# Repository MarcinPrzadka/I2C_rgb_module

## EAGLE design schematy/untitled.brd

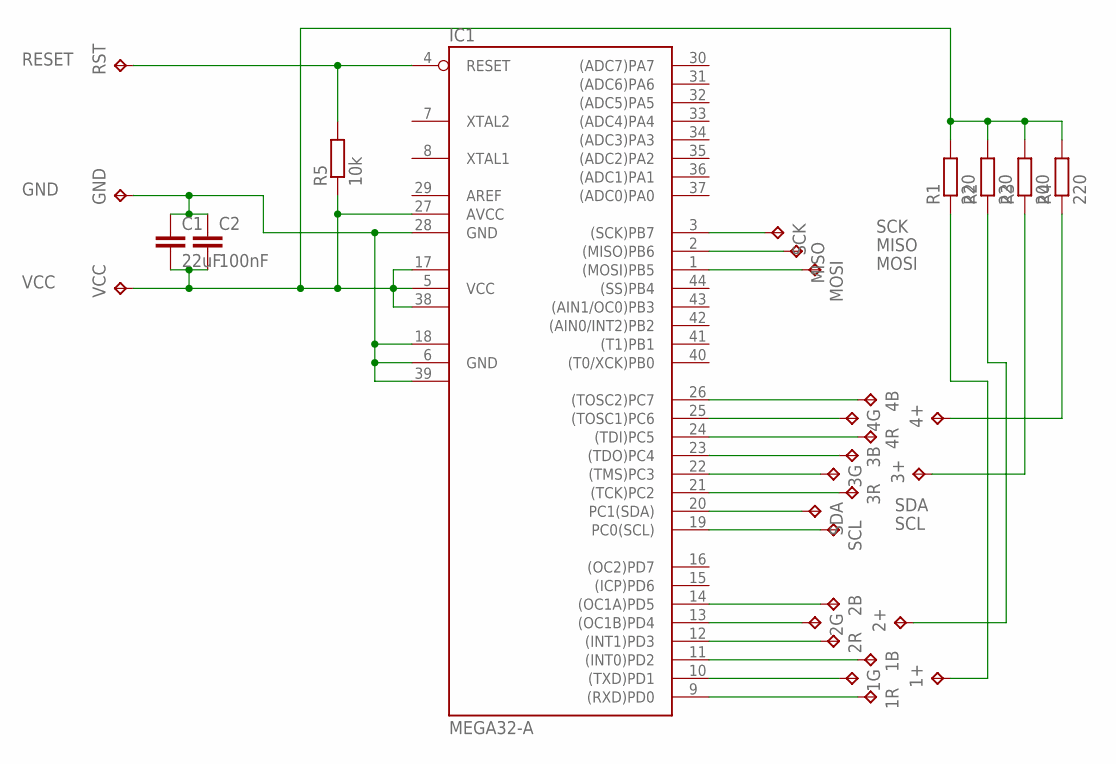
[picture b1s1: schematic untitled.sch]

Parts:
1+, 1B, 1G, 1R, 2+, 2B, 2G, 2R, 3+, 3B, 3G, 3R, 4+, 4B, 4G, 4R: TPTP19SQ; TP19SQ
C1: 22uF; C025-024X044
C2: 100nF; C025-024X044
GND: TPTP19SQ; TP19SQ
IC1: MEGA32-A; TQFP44
MISO: TPTP19SQ; TP19SQ
MOSI: TPTP19SQ; TP19SQ
R1, R2, R4: 220; M0805
R3: 200; M0805
R5: 10k; M0805
RST: TPTP19SQ; TP19SQ
SCK: SCK; TP19SQ
SCL: TPTP19SQ; TP19SQ
SDA: TPTP19SQ; TP19SQ
VCC: TPTP19SQ; TP19SQ

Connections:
GND: C1.1, C2.1, GND.TP, IC1.6 (GND), IC1.18 (GND1), IC1.28 (GND), IC1.39 (GND2)
MISO: IC1.2 ((MISO)PB6), MISO.TP
MOSI: IC1.1 ((MOSI)PB5), MOSI.TP
unnamed: 1R.TP, IC1.9 ((RXD)PD0)
unnamed: 1G.TP, IC1.10 ((TXD)PD1)
unnamed: 1B.TP, IC1.11 ((INT0)PD2)
unnamed: 2R.TP, IC1.12 ((INT1)PD3)
unnamed: 2G.TP, IC1.13 ((OC1B)PD4)
unnamed: 2B.TP, IC1.14 ((OC1A)PD5)
unnamed: 3R.TP, IC1.21 ((TCK)PC2)
unnamed: 3G.TP, IC1.22 ((TMS)PC3)
unnamed: 3B.TP, IC1.23 ((TDO)PC4)
unnamed: 4R.TP, IC1.24 ((TDI)PC5)
unnamed: 4G.TP, IC1.25 ((TOSC1)PC6)
unnamed: 4B.TP, IC1.26 ((TOSC2)PC7)
unnamed: 1+.TP, R1.1
unnamed: 2+.TP, R2.1
unnamed: 3+.TP, R3.1
unnamed: 4+.TP, R4.1
RESET: IC1.4 (RESET), R5.2, RST.TP
SCK: IC1.3 ((SCK)PB7), SCK.TP
SCL: IC1.19 (PC0(SCL)), SCL.TP
SDA: IC1.20 (PC1(SDA)), SDA.TP
VCC: C1.2, C2.2, IC1.5 (VCC), IC1.17 (VCC1), IC1.27 (AVCC), IC1.38 (VCC2), R1.2, R2.2, R3.2, R4.2, R5.1, VCC.TP

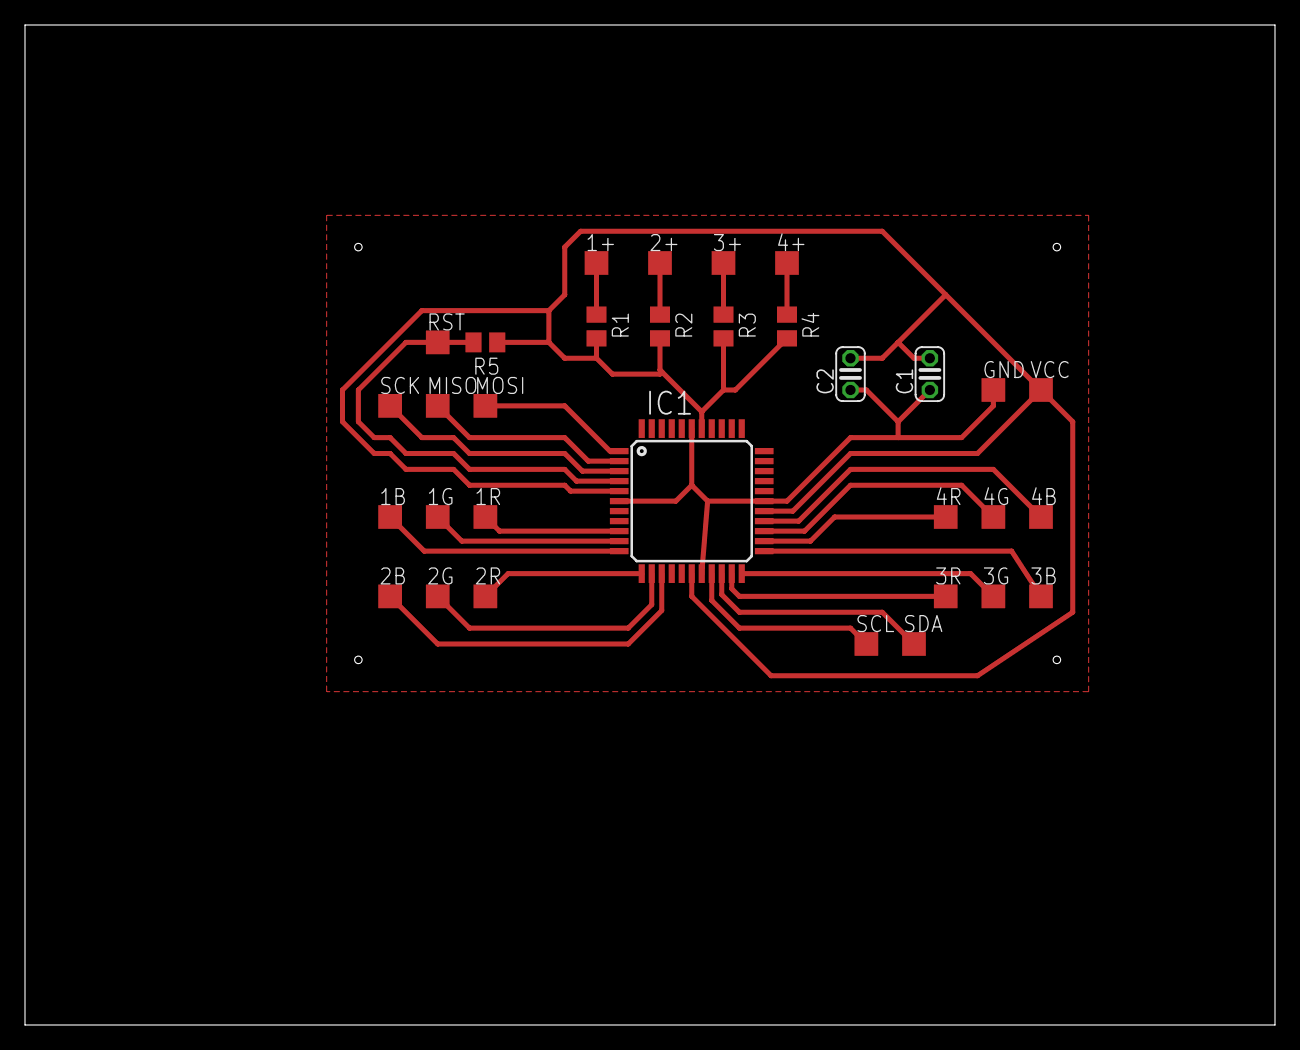
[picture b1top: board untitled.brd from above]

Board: 2 copper layers, 100.0 x 80.0 mm, 32 parts (0 on the bottom side), 24 nets.

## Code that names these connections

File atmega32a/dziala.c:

#include <avr/io.h>
#include <util/delay.h>
#include <avr/interrupt.h>

volatile uint8_t pwm1R, pwm1G, pwm1B, pwm2R, pwm2G, pwm2B,pwm3R, pwm3G, pwm3B, pwm4R, pwm4G, pwm4B;

int main(void)
{
	
	DDRB |= (1<<PB3);

	TCCR0 |= (1<<WGM01)|(1<<WGM00);		// tryb Fast PWM
	TCCR0 |= (1<<COM01);				// clear at TOP
	TCCR0 |= (1<<CS00);					// preskaler = 1
	OCR0=255;
								// wygaszenie diody w kanale PWM
	DDRD |= (1<<PD0)|(1<<PD1)|(1<<PD2)|(1<<PD3)|(1<<PD4)|(1<<PD5);
	DDRC |= (1<<PC2)|(1<<PC3)|(1<<PC4)|(1<<PC5)|(1<<PC6)|(1<<PC7);
	PORTD |= (1<<PD0)|(1<<PD1)|(1<<PD2)|(1<<PD3)|(1<<PD4)|(1<<PD5);
	PORTC |= (1<<PC2)|(1<<PC3)|(1<<PC4)|(1<<PC5)|(1<<PC6)|(1<<PC7);

	TCCR2 |= (1<<WGM21);	// tryb  CTC
	TCCR2 |= (1<<CS20);		// preskaler = 1
	OCR2 = 199;				// dodatkowy podzia³ czêsttotliwoci przez 200
	TIMSK |= (1<<OCIE2);	// zezwolenie na przerwanie CompareMatch
	sei();				// odblokowanie globalne przerwañ
	unsigned char data;
	TWI_init_slave();

	while(1)
	{
		//data = TWI_read_slave();
		//if(data == "255") pwm1G = 255;
		//Police();
		
		GrenLantern();
		
	}

}

// Funkcje swiecace

Police(){
		LedClean();
		pwm1R=255;
		pwm2B=255;
		pwm1B=0;
		pwm2R=0;
		_delay_ms(3);
		pwm1R=0;
		pwm2B=0;
		pwm1B=255;
		pwm2R=255;
		_delay_ms(3);
}
GreenLantern(){
	
	LedClean();
	pwm1G = 255;
	pwm2G = 255;
	pwm3G = 255;
	pwm4G = 255;

}

LedClean(){
	pwm1R = 0;
	pwm1B = 0;
	pwm1G = 0;
	pwm2R = 0;
	pwm2B = 0;
	pwm2G = 0;
	pwm3R = 0;
	pwm3B = 0;
	pwm3G = 0;
	pwm4R = 0;
	pwm4B = 0;
	pwm4G = 0;

}




ISR( TIMER2_COMP_vect ) // cia³o procedury obs³ugi przerwania Compare Match Timera2
{
	static uint8_t cnt; 
	if(cnt>=pwm1R) PORTD |= (1<<PD0); else PORTD &= ~(1<<PD0);
	if(cnt>=pwm1G) PORTD |= (1<<PD1); else PORTD &= ~(1<<PD1);
	if(cnt>=pwm1B) PORTD |= (1<<PD2); else PORTD &= ~(1<<PD2);
	if(cnt>=pwm2R) PORTD |= (1<<PD3); else PORTD &= ~(1<<PD3);
	if(cnt>=pwm2G) PORTD |= (1<<PD4); else PORTD &= ~(1<<PD4);
	if(cnt>=pwm2B) PORTD |= (1<<PD5); else PORTD &= ~(1<<PD5);
	if(cnt>=pwm3R) PORTC |= (1<<PC2); else PORTC &= ~(1<<PC2);
	if(cnt>=pwm3G) PORTC |= (1<<PC3); else PORTC &= ~(1<<PC3);
	if(cnt>=pwm3B) PORTC |= (1<<PC4); else PORTC &= ~(1<<PC4);
	if(cnt>=pwm4R) PORTC |= (1<<PC5); else PORTC &= ~(1<<PC5);
	if(cnt>=pwm4G) PORTC |= (1<<PC6); else PORTC &= ~(1<<PC6);
	if(cnt>=pwm4B) PORTC |= (1<<PC7); else PORTC &= ~(1<<PC7);
	cnt++;	
}

void TWI_init_slave(void) // Function to initilaize slave
{
    TWAR=0x20;    // Fill slave address to TWAR
} 

void TWI_match_read_slave(void) //Function to match the slave address and slave dirction bit(read)
{
    while((TWSR & 0xF8)!= 0x60)  // Loop till correct acknoledgement have been received
    {
        // Get acknowlegement, Enable TWI, Clear TWI interrupt flag
        TWCR=(1<<TWEA)|(1<<TWEN)|(1<<TWINT);    
        while (!(TWCR & (1<<TWINT)));  // Wait for TWINT flag
    }
} 

void TWI_read_slave(void)
{
	unsigned char recv_data;
    // Clear TWI interrupt flag,Get acknowlegement, Enable TWI
    TWCR= (1<<TWINT)|(1<<TWEA)|(1<<TWEN);    
    while (!(TWCR & (1<<TWINT)));    // Wait for TWINT flag
    while((TWSR & 0xF8)!=0x80);        // Wait for acknowledgement
    recv_data=TWDR;                    // Get value from TWDR
    PORTB=recv_data;                // send the receive value on PORTB
}
